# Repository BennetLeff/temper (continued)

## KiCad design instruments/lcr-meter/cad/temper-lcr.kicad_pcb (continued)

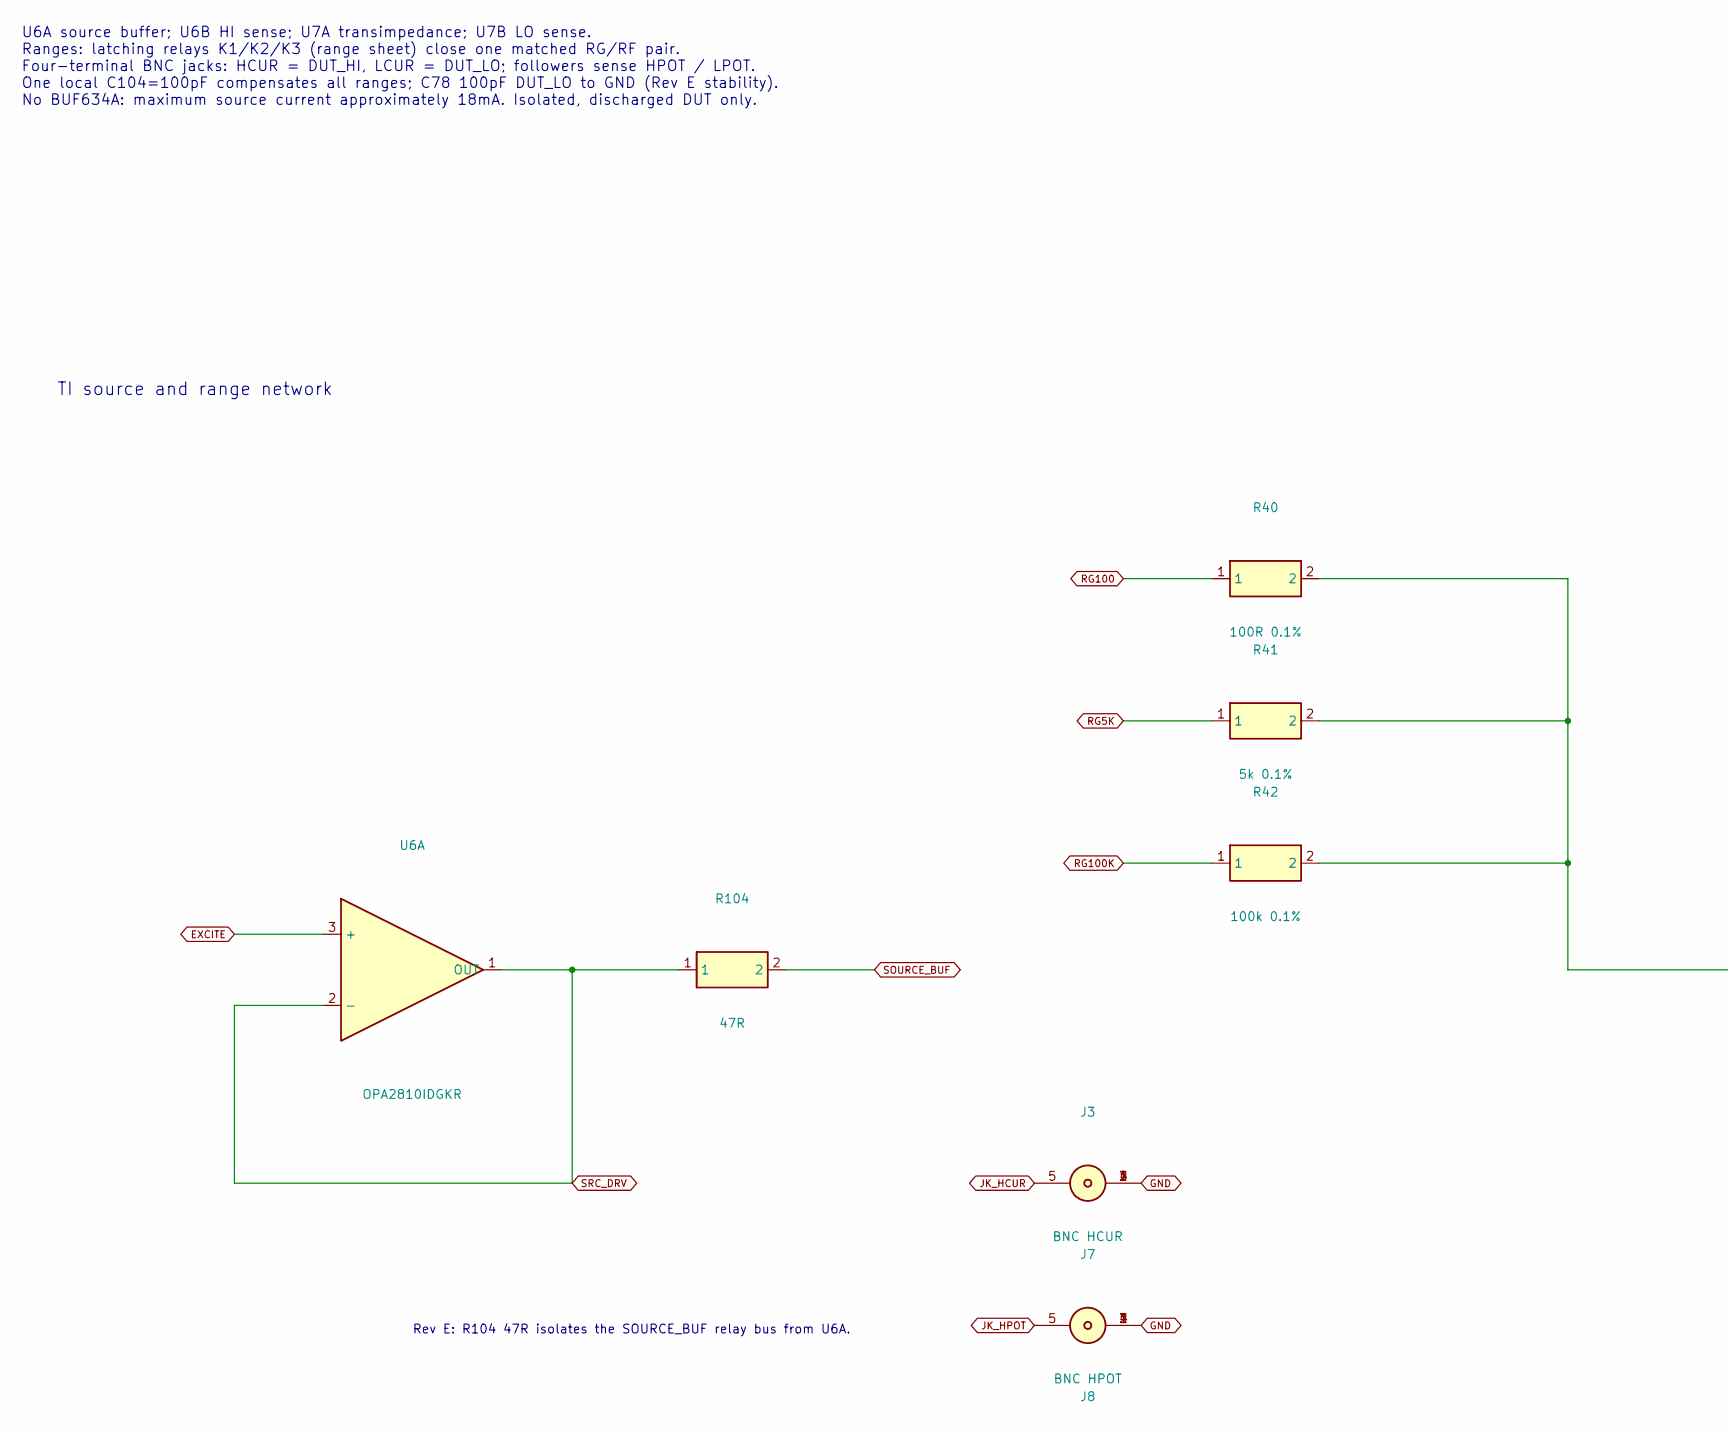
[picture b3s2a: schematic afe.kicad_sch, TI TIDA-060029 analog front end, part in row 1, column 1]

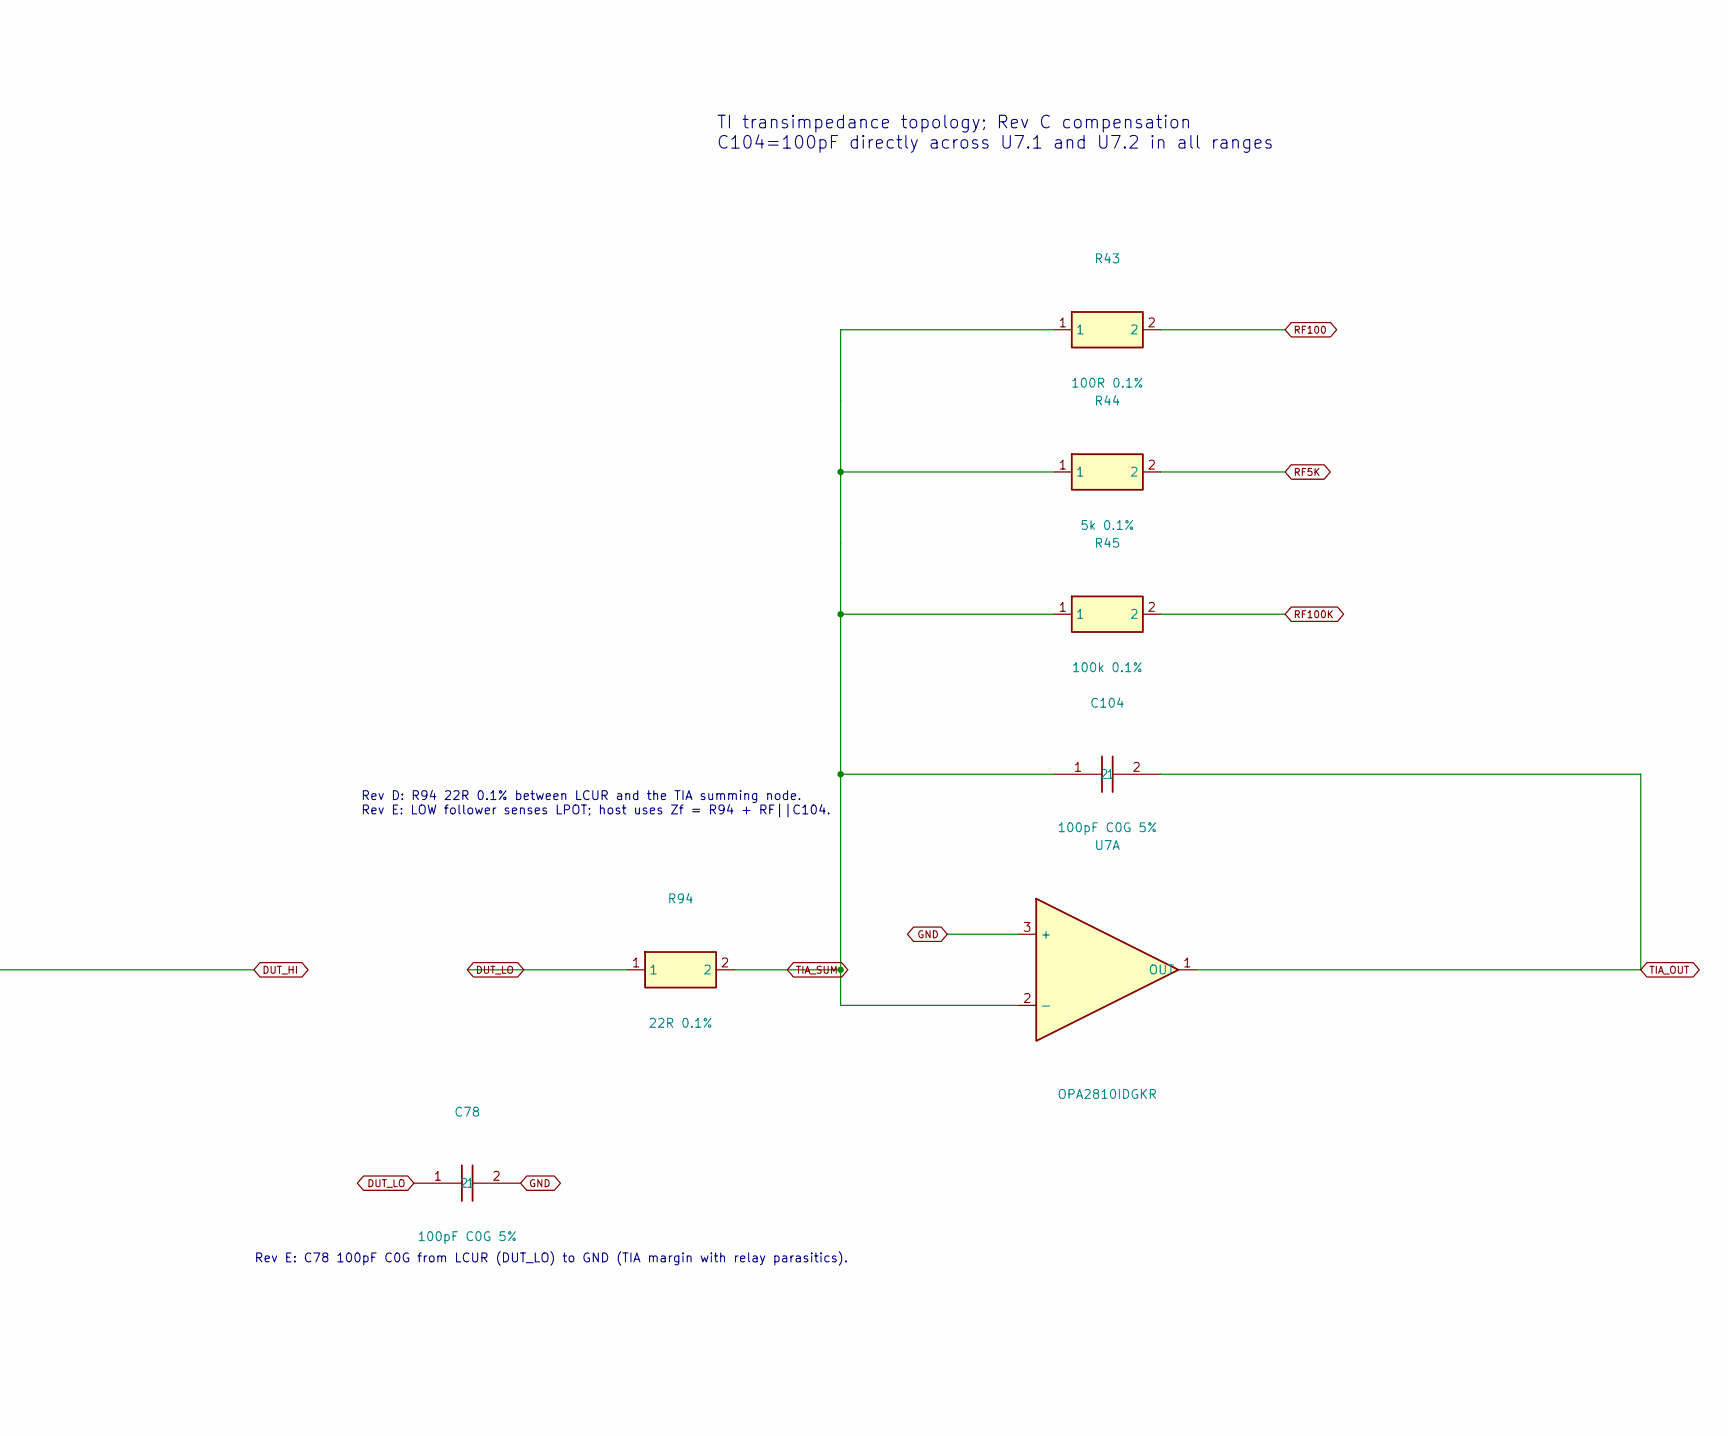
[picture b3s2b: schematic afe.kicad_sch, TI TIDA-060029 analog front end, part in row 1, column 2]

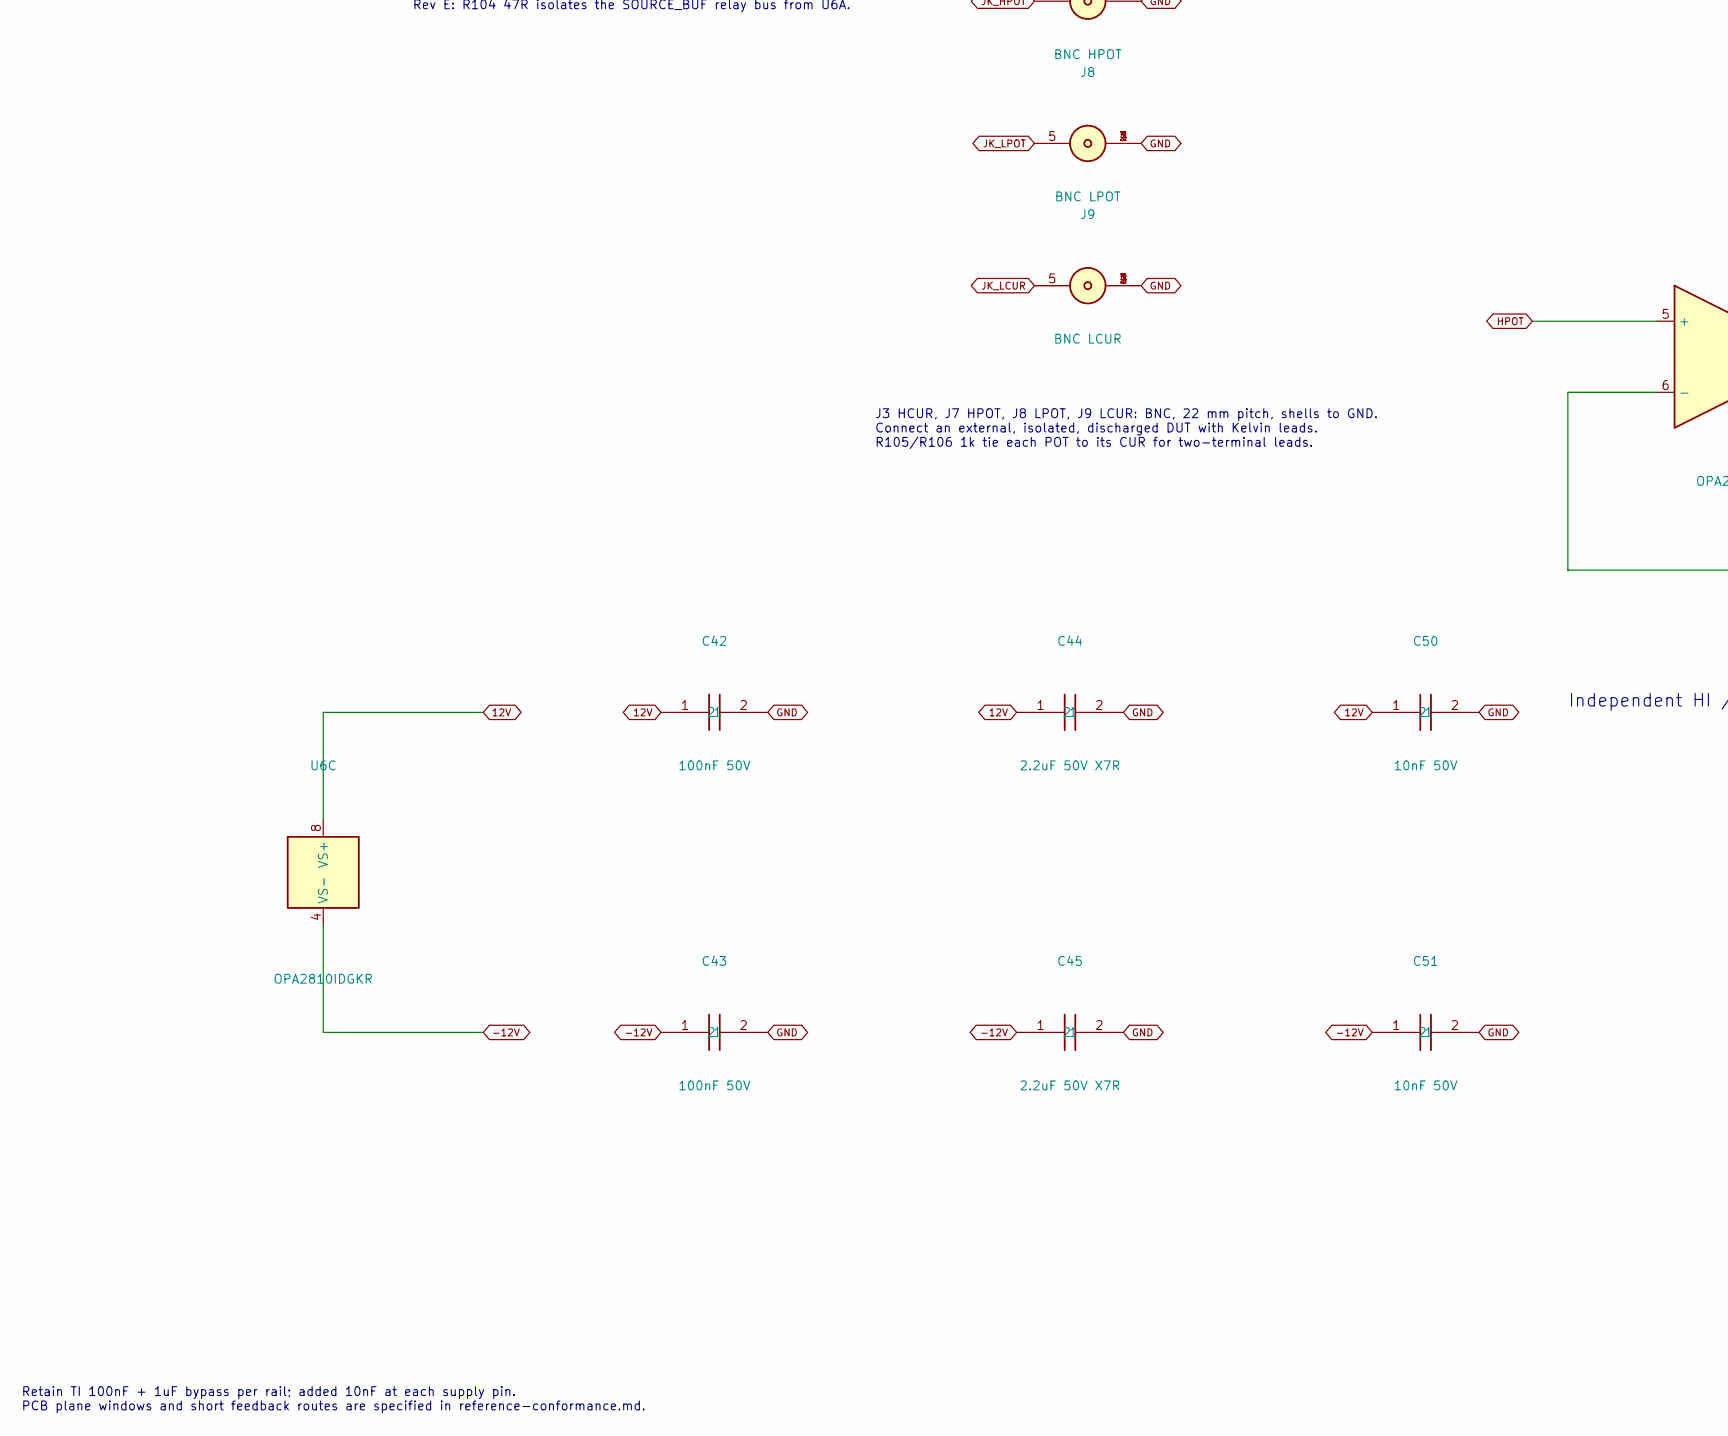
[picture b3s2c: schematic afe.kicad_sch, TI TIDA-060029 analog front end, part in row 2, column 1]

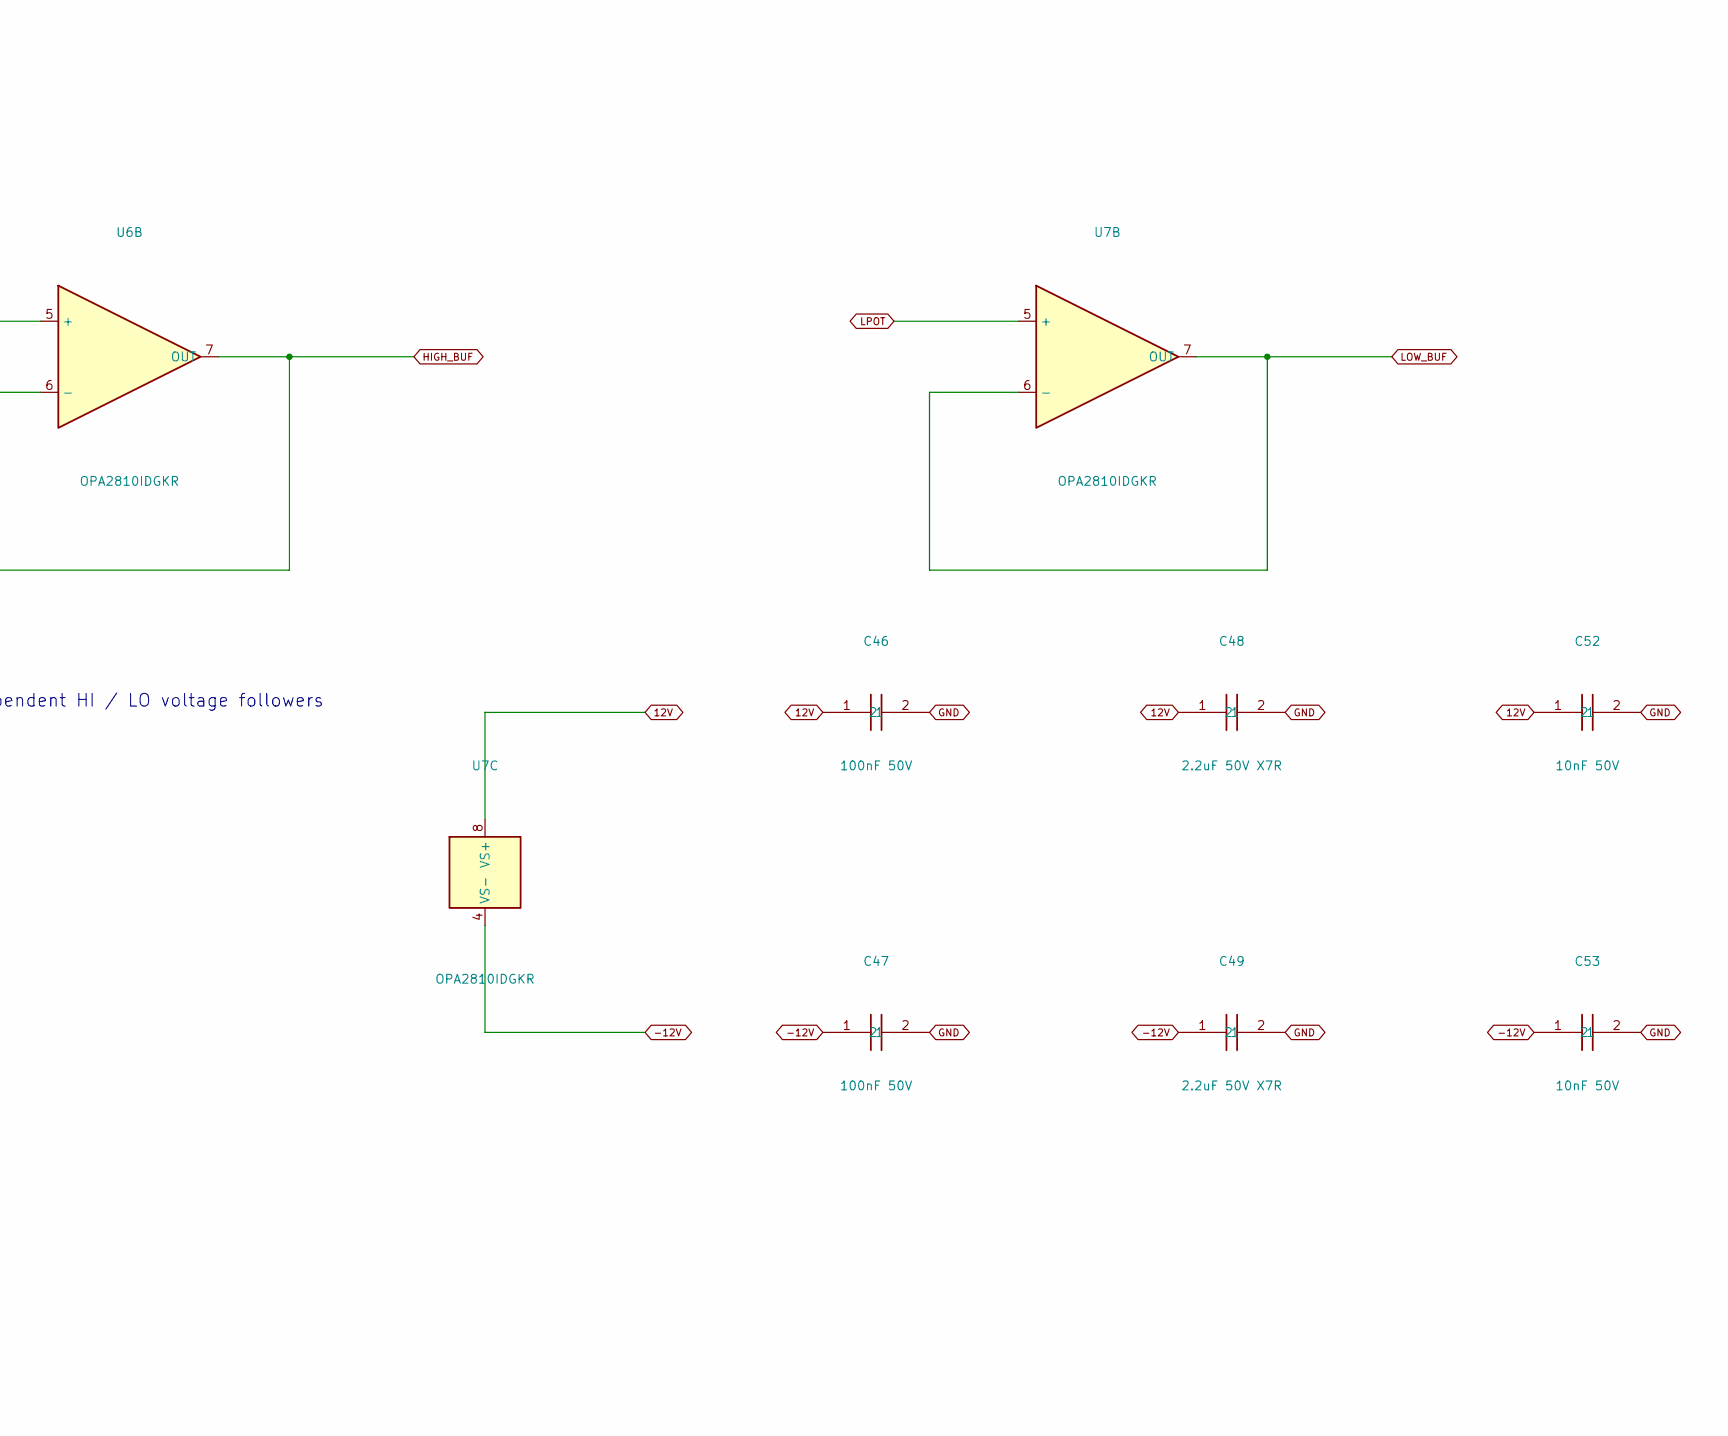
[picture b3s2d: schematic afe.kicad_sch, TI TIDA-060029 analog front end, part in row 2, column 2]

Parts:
C42, C43, C46, C47: 100nF 50V; C_0603_1608Metric; MPN CC0603KRX7R9BB104; LCSC C14663
C44, C45, C48, C49: 2.2uF 50V X7R; C_0805_2012Metric; MPN CC0805KKX7R9BB225; LCSC C125847
C50, C51, C52, C53: 10nF 50V; C_0603_1608Metric; MPN 0603B103K500NT; LCSC C57112
C78, C104: 100pF C0G 5%; C_0603_1608Metric; MPN CL10C101JB8NNNC; LCSC C14858
J3: BNC HCUR; BNC_SAMZO_KYWE-295-W4-N_Horizontal; MPN BNC-KYWE-295-W4-N; LCSC C41416668
J7: BNC HPOT; BNC_SAMZO_KYWE-295-W4-N_Horizontal; MPN BNC-KYWE-295-W4-N; LCSC C41416668
J8: BNC LPOT; BNC_SAMZO_KYWE-295-W4-N_Horizontal; MPN BNC-KYWE-295-W4-N; LCSC C41416668
J9: BNC LCUR; BNC_SAMZO_KYWE-295-W4-N_Horizontal; MPN BNC-KYWE-295-W4-N; LCSC C41416668
R40, R43: 100R 0.1%; R_0603_1608Metric; MPN RT0603BRD07100RL; LCSC C122970
R41, R44: 5k 0.1%; R_0603_1608Metric; MPN AR03BTCX5001; LCSC C2828621
R42, R45: 100k 0.1%; R_0603_1608Metric; MPN RT0603BRD07100KL; LCSC C122538
R94: 22R 0.1%; R_0603_1608Metric; MPN RT0603BRD0722RL; LCSC C861239
R104: 47R; R_0603_1608Metric; MPN 0603WAF470JT5E; LCSC C23182
U6, U7: OPA2810IDGKR; VSSOP-8_3x3mm_P0.65mm; MPN OPA2810IDGKR; LCSC C2864204

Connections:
12V: C42.1, C44.1, C46.1, C48.1, C50.1, C52.1, U6.8 (VS+), U7.8 (VS+); also elsewhere on the board
-12V: C43.1, C45.1, C47.1, C49.1, C51.1, C53.1, U6.4 (VS-), U7.4 (VS-); also elsewhere on the board
DUT_HI: R40.2, R41.2, R42.2; also elsewhere on the board
DUT_LO: C78.1, R94.1; also elsewhere on the board
EXCITE: U6.3 (+); also elsewhere on the board
GND: C42.2, C43.2, C44.2, C45.2, C46.2, C47.2, C48.2, C49.2, C50.2, C51.2, C52.2, C53.2, C78.2, J3.1, J3.2, J3.3, J3.4, J7.1, J7.2, J7.3, J7.4, J8.1, J8.2, J8.3, J8.4, J9.1, J9.2, J9.3, J9.4, U7.3 (+); also elsewhere on the board
HIGH_BUF: U6.6 (-), U6.7 (OUT); also elsewhere on the board
HPOT: U6.5 (+); also elsewhere on the board
JK_HCUR: J3.5; also elsewhere on the board
JK_HPOT: J7.5; also elsewhere on the board
JK_LCUR: J9.5; also elsewhere on the board
JK_LPOT: J8.5; also elsewhere on the board
LOW_BUF: U7.6 (-), U7.7 (OUT); also elsewhere on the board
LPOT: U7.5 (+); also elsewhere on the board
RF5K: R44.2; also elsewhere on the board
RF100: R43.2; also elsewhere on the board
RF100K: R45.2; also elsewhere on the board
RG5K: R41.1; also elsewhere on the board
RG100: R40.1; also elsewhere on the board
RG100K: R42.1; also elsewhere on the board
SOURCE_BUF: R104.2; also elsewhere on the board
SRC_DRV: R104.1, U6.1 (OUT), U6.2 (-)
TIA_OUT: C104.2, U7.1 (OUT); also elsewhere on the board
TIA_SUM: C104.1, R43.1, R44.1, R45.1, R94.2, U7.2 (-)

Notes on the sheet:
U6A source buffer; U6B HI sense; U7A transimpedance; U7B LO sense. Ranges: latching relays K1/K2/K3 (range sheet) close one matched RG/RF pair. Four-terminal BNC jacks: HCUR = DUT_HI, LCUR = DUT_LO; followers sense HPOT / LPOT. One local C104=100pF compensates all ranges; C78 100pF DUT_LO to GND (R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
TI source and range network
Rev E: R104 47R isolates the SOURCE_BUF relay bus from U6A.
J3 HCUR, J7 HPOT, J8 LPOT, J9 LCUR: BNC, 22 mm pitch, shells to GND. Connect an external, isolated, discharged DUT with Kelvin leads. R105/R106 1k tie each POT to its CUR for two-terminal leads.
Rev D: R94 22R 0.1% between LCUR and the TIA summing node. Rev E: LOW follower senses LPOT; host uses Zf = R94 + RF||C104.
Rev E: C78 100pF C0G from LCUR (DUT_LO) to GND (TIA margin with relay parasitics).
TI transimpedance topology; Rev C compensation C104=100pF directly across U7.1 and U7.2 in all ranges
Independent HI / LO voltage followers
Retain TI 100nF + 1uF bypass per rail; added 10nF at each supply pin. PCB plane windows and short feedback routes are specified in reference-conformance.md.

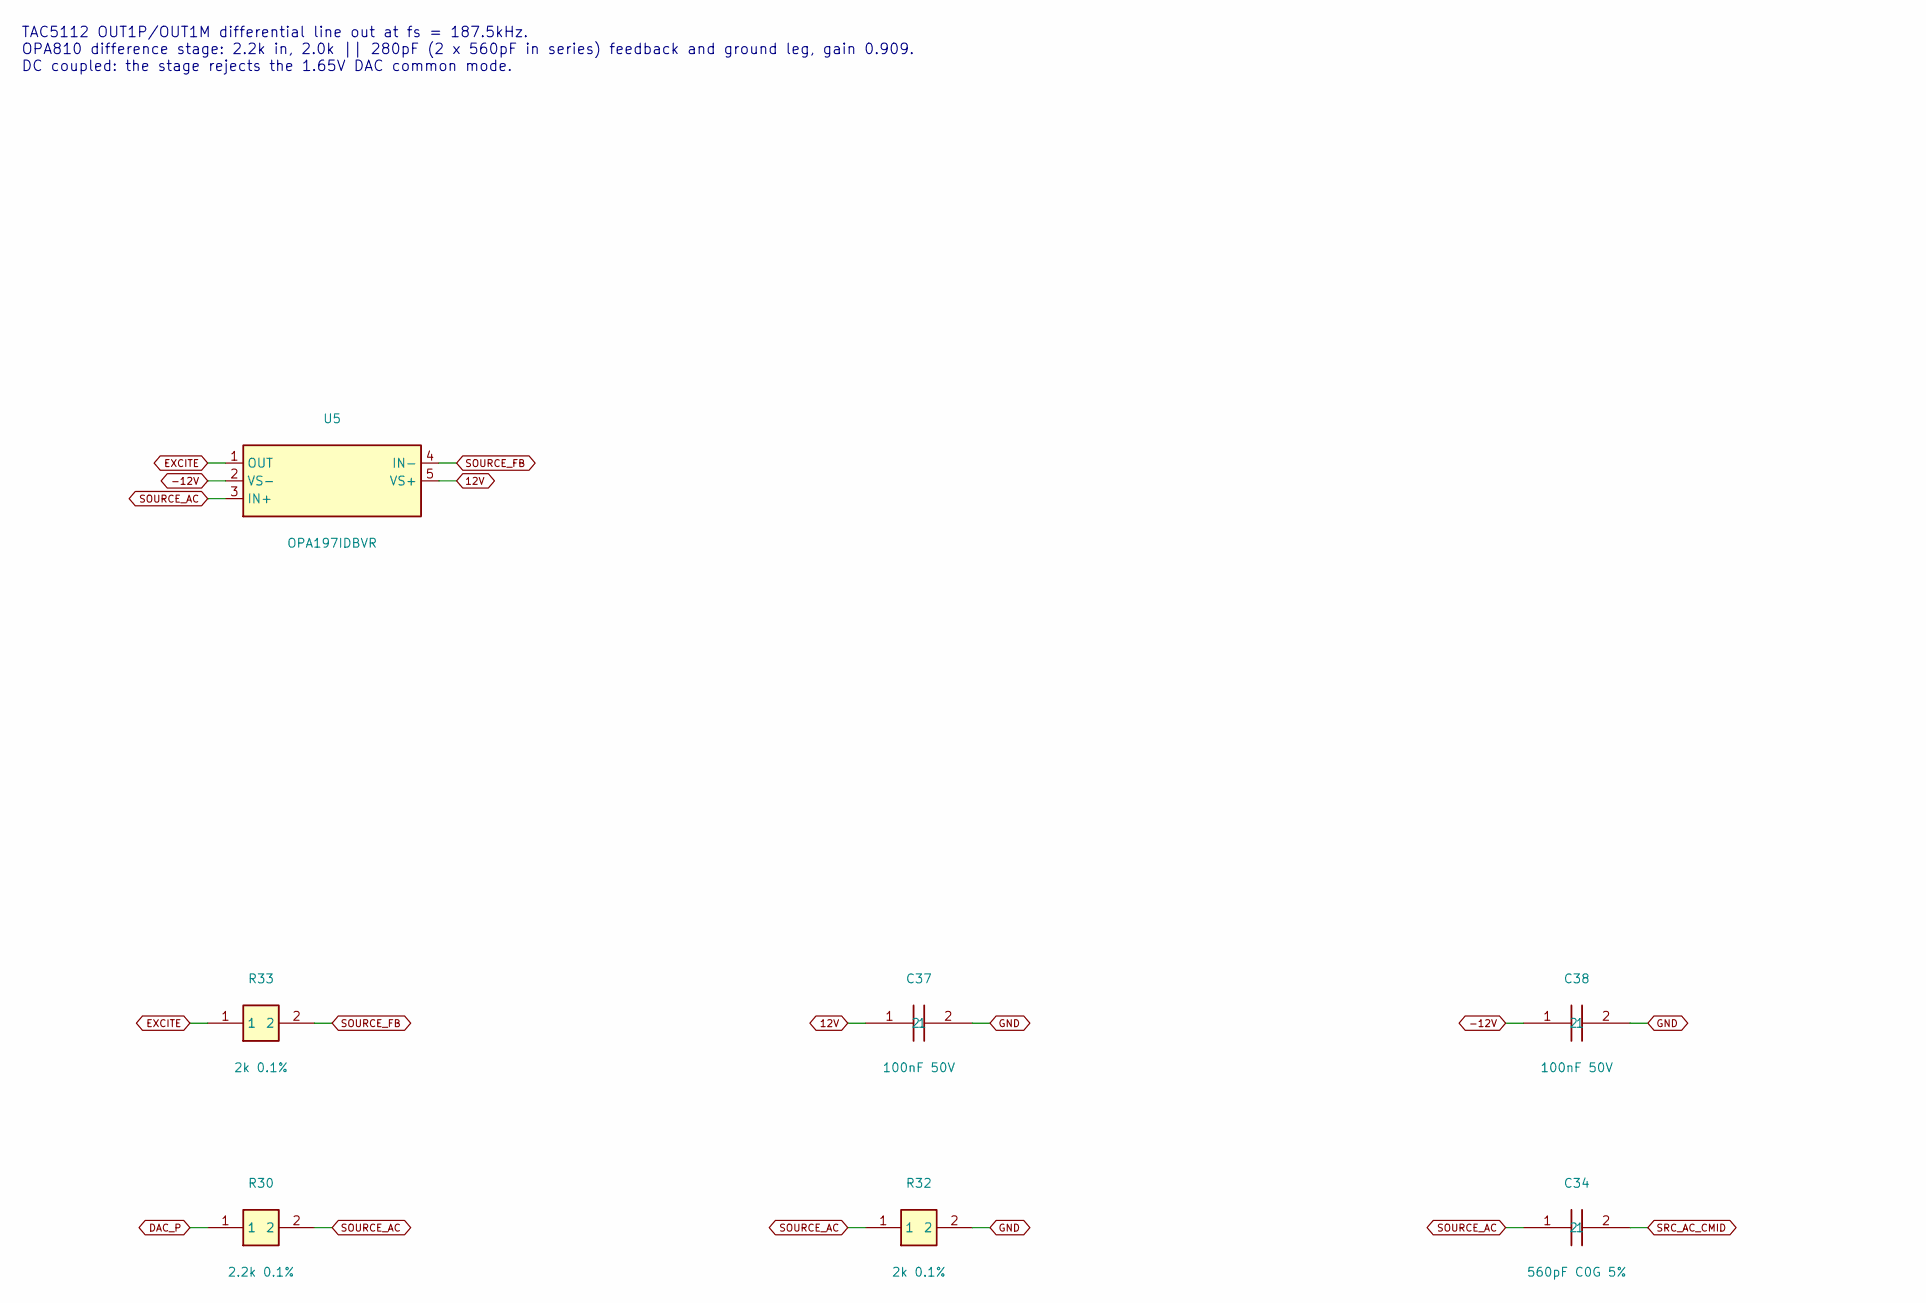
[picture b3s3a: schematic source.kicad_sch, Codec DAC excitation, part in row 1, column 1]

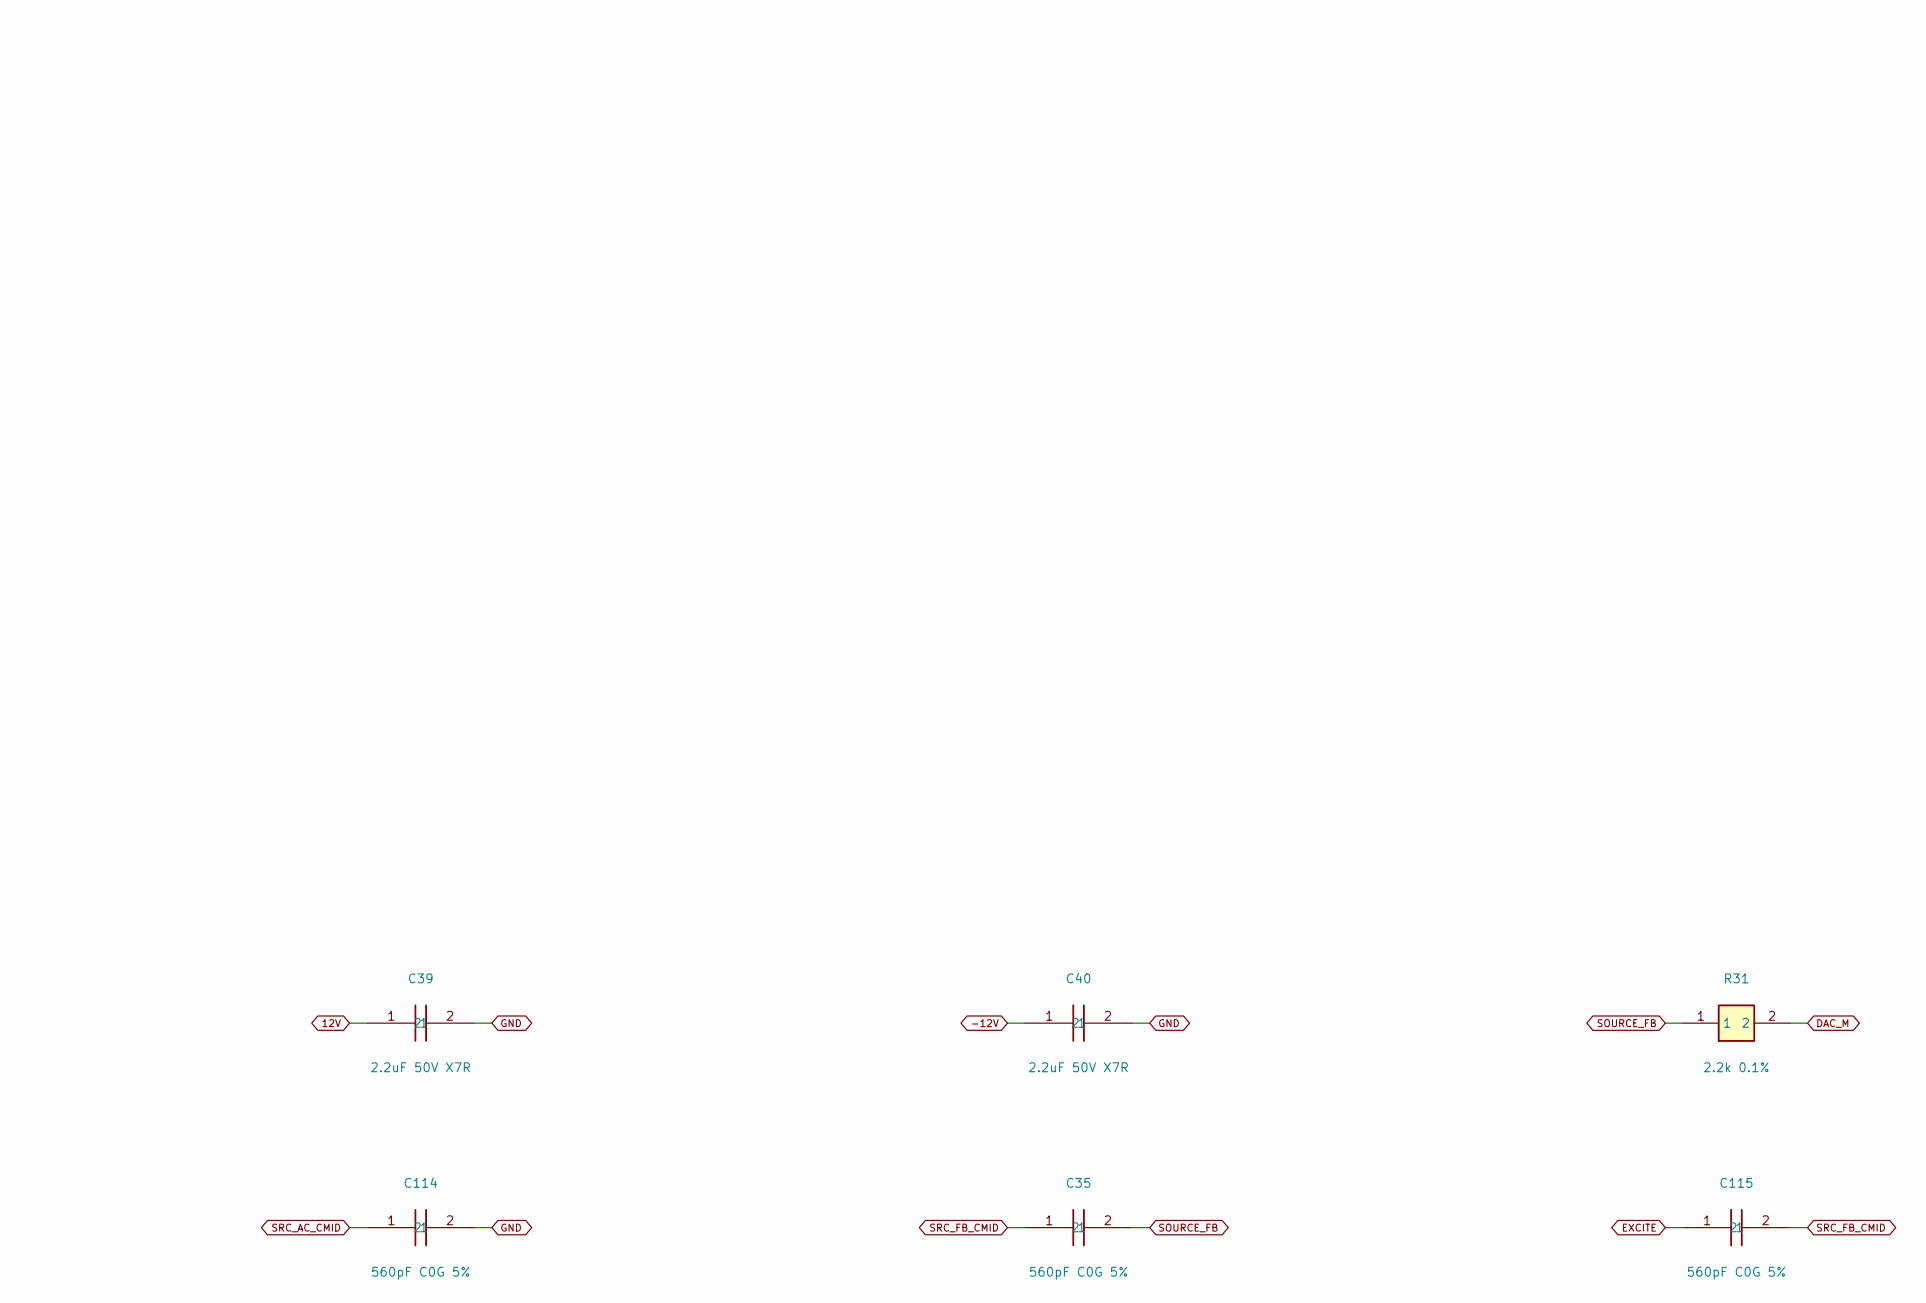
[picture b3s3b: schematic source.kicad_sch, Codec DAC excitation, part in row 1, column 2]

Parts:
C34, C35, C114, C115: 560pF C0G 5%; C_0603_1608Metric; MPN CC0603JRNPO9BN561; LCSC C107054
C37, C38: 100nF 50V; C_0603_1608Metric; MPN CC0603KRX7R9BB104; LCSC C14663
C39, C40: 2.2uF 50V X7R; C_0805_2012Metric; MPN CC0805KKX7R9BB225; LCSC C125847
R30, R31: 2.2k 0.1%; R_0603_1608Metric; MPN RT0603BRD072K2L; LCSC C861295
R32, R33: 2k 0.1%; R_0603_1608Metric; MPN AR03BTCX2001; LCSC C318130
U5: OPA197IDBVR; SOT-23-5; MPN OPA197IDBVR; LCSC C221351

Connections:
12V: C37.1, C39.1, U5.5 (VS+); also elsewhere on the board
-12V: C38.1, C40.1, U5.2 (VS-); also elsewhere on the board
DAC_M: R31.2; also elsewhere on the board
DAC_P: R30.1; also elsewhere on the board
EXCITE: C115.1, R33.1, U5.1 (OUT); also elsewhere on the board
GND: C37.2, C38.2, C39.2, C40.2, C114.2, R32.2; also elsewhere on the board
SOURCE_AC: C34.1, R30.2, R32.1, U5.3 (IN+)
SOURCE_FB: C35.2, R31.1, R33.2, U5.4 (IN-)
SRC_AC_CMID: C34.2, C114.1
SRC_FB_CMID: C35.1, C115.2

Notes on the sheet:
TAC5112 OUT1P/OUT1M differential line out at fs = 187.5kHz. OPA810 difference stage: 2.2k in, 2.0k || 280pF (2 x 560pF in series) feedback and ground leg, gain 0.909. DC coupled: the stage rejects the 1.65V DAC common mode.
